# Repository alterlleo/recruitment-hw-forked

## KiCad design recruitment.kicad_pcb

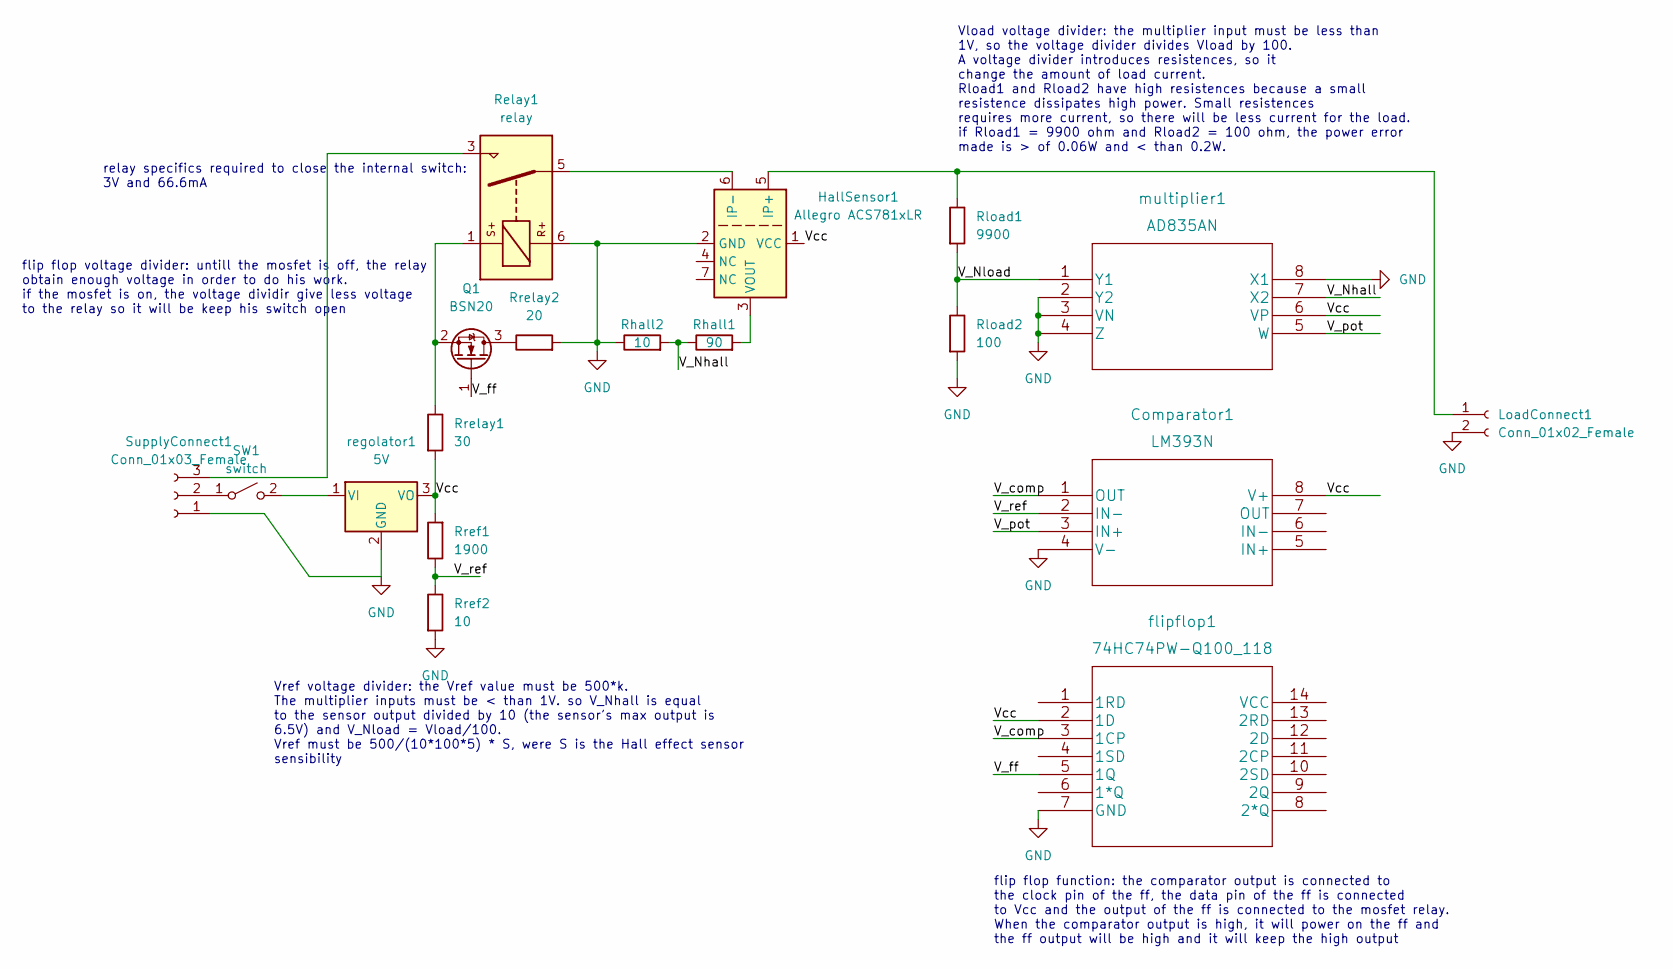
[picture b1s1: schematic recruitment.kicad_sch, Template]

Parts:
Comparator1: LM393N
HallSensor1: Allegro ACS781xLR; Allegro_PSOF-7_4.8x6.4mm_P1.60mm
LoadConnect1: Conn_01x02_Female; PinHeader_1x02_P2.00mm_Vertical
Q1: BSN20; SOT-23
Relay1: relay; Relay_1P1T_NO_10x24x18.8mm_Panasonic_ADW11xxxxW_THT
Rhall1: 90; R_2816_7142Metric
Rhall2: 10; R_2816_7142Metric
Rload1: 9900; R_2816_7142Metric
Rload2: 100; R_2816_7142Metric
Rref1: 1900; R_2816_7142Metric
Rref2: 10; R_2816_7142Metric
Rrelay1: 30; R_2816_7142Metric
Rrelay2: 20; R_2816_7142Metric
SW1: switch; SW_DIP_SPSTx01_Slide_6.7x4.1mm_W6.73mm_P2.54mm_LowProfile_J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
SupplyConnect1: Conn_01x03_Female; PinHeader_1x03_P2.00mm_Vertical
flipflop1: 74HC74PW-Q100_118
multiplier1: AD835AN
regolator1: 5V; TO-220-3_Vertical

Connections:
/V_Nhall: Rhall1.1, Rhall2.2, multiplier1.7 (X2)
/V_Nload: Rload1.2, Rload2.1, multiplier1.1 (Y1)
/V_comp: Comparator1.1 (OUT), flipflop1.3 (1CP)
/V_ff: Q1.1 (G), flipflop1.5 (1Q)
/V_pot: Comparator1.3 (IN+), multiplier1.5 (W)
/V_ref: Comparator1.2 (IN-), Rref1.1, Rref2.1
/Vcc: Comparator1.8 (V+), HallSensor1.1 (VCC), Rref1.2, Rrelay1.2, flipflop1.2 (1D), multiplier1.6 (VP), regolator1.3 (VO)
GND: Comparator1.4 (V-), HallSensor1.2 (GND), LoadConnect1.2, Relay1.6, Rhall2.1, Rload2.2, Rref2.2, Rrelay2.2, SupplyConnect1.1, flipflop1.7 (GND), multiplier1.2 (Y2), multiplier1.3 (VN), multiplier1.4 (Z), multiplier1.8 (X1), regolator1.2 (GND)
unnamed: HallSensor1.3 (VOUT), Rhall1.2
unnamed: HallSensor1.5 (IP+), LoadConnect1.1, Rload1.1
unnamed: HallSensor1.6 (IP-), Relay1.5
unnamed: Q1.2 (S), Relay1.1, Rrelay1.1
unnamed: Q1.3 (D), Rrelay2.1
unnamed: Relay1.3, SupplyConnect1.3
unnamed: SW1.1 (A), SupplyConnect1.2
unnamed: SW1.2 (B), regolator1.1 (VI)

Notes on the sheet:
Vref voltage divider: the Vref value must be 500*k. The multiplier inputs must be < than 1V. so V_Nhall is equal to the sensor output divided by 10 (the sensor's max output is 6.5V) and V_Nload = Vload/100. Vref must be 500/(10*100*5) * S, were S is the Hall effect sensor sensibility
Vload voltage divider: the multiplier input must be less than 1V, so the voltage divider divides Vload by 100. A voltage divider introduces resistences, so it change the amount of load current. Rload1 and Rload2 have high resistences because a small resistence dissipates high power. Small resistenc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
relay specifics required to close the internal switch: 3V and 66.6mA
flip flop voltage divider: untill the mosfet is off, the relay obtain enough voltage in order to do his work. if the mosfet is on, the voltage dividir give less voltage to the relay so it will be keep his switch open
flip flop function: the comparator output is connected to the clock pin of the ff, the data pin of the ff is connected to Vcc and the output of the ff is connected to the mosfet relay. When the comparator output is high, it will power on the ff and the ff output will be high and it will keep the hi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

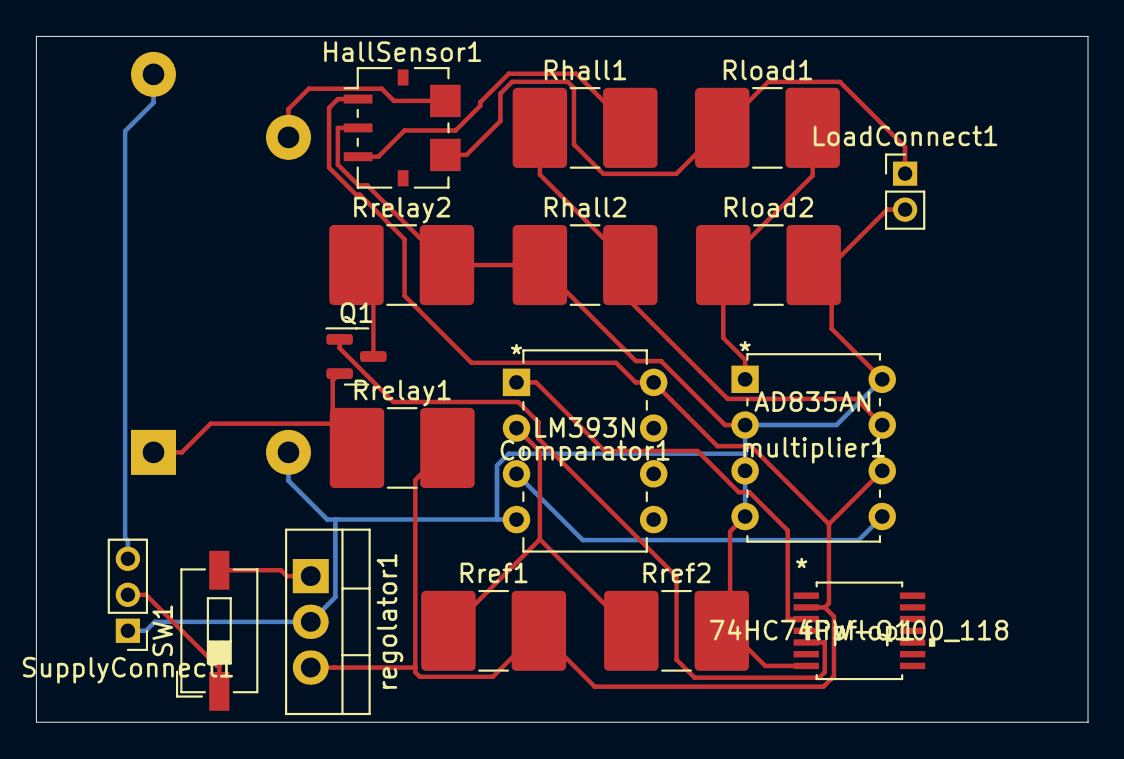
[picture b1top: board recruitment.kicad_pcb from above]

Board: 2 copper layers, 58.4 x 38.1 mm, 18 parts (1 on the bottom side), 16 nets.

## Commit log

2023-03-08 first setup: add ideas' text
2023-03-09 first circuit, TODO: check properly the voltage and the power
2023-03-09 setup for the win
2023-03-09 ad633 imported
2023-03-09 added AD633, TODO: do it in a better shape; add values
2023-03-10 R values added, TODO: understand transistors
2023-03-10 add R values, TODO: understand transistors
2023-03-10 add switch, TODO: check loop transistor
2023-03-11 check transistor, TODO: R values and multiplier supply
2023-03-11 TODO: ad633 footprint
2023-03-12 footprints/autorouting done, TODO: understand transistor and optimize pcb shape
2023-03-13 better shape + MOSFET, TODO: adjust multiplier, it's better AD534
2023-03-13 correct multiplier, TODO: check MOSFET
2023-03-14 TODO: mosfet depletion channel p
2023-03-15 remove casino, TODO: add flipflp sr, check AD834jn
2023-03-15 added flipflop, TODO: connect Vff to MOSFET relay
2023-03-17 add AD835, correct voltages and wires
2023-03-17 routing, first release
2023-03-18 check
2023-03-18 check R relay
2023-03-18 check Rref
2023-03-19 ses with and without vias
2023-03-19 add gerbers
2023-03-20 add datasheets
2023-03-20 mosfet datasheet
2023-04-24 forgotten commit :)

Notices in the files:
parts and their libraries:
Copyright 2021 Accelerated Designs. All rights reserved.
